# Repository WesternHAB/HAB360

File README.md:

# HAB360

This repository is for WesternU HAB team's VR balloon project. The goal is to fly 360° cameras on a balloon platform. The resulting video/images could then be viewed using VR cameras for outreach purposes.

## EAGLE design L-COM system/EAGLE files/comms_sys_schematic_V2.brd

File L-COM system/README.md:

# L-COM
This system is intended to serve as the communications system for high-altitude balloons and other devices in need of wireless communications.

The L-COM device may either be used as an attached radio by sending/receiving messages on the UART interface, or it may be programmed to be used as the sole onboard controller.

A python-based GUI is provided to allow full control over the L-COM device via a laptop, and may be adapted to be used as a groundstation.

## L-COM

 boards")

## Testing results
Initial testing involved the use of low-range, data-rate maximizing settings, while travelling throughout an urban environment. The L-COM modules behaved as expected, and the results produced were nominal for the environment. Communication was relatively unhindered by most residential buildings, and only encountered issues when blocked by large hills or certain non-residential buildings built with different materials.

Remaining testing involves long-range settings in a rural environment in order to provide a better estimate of how effective it will be for communicating with high-altitude balloons.

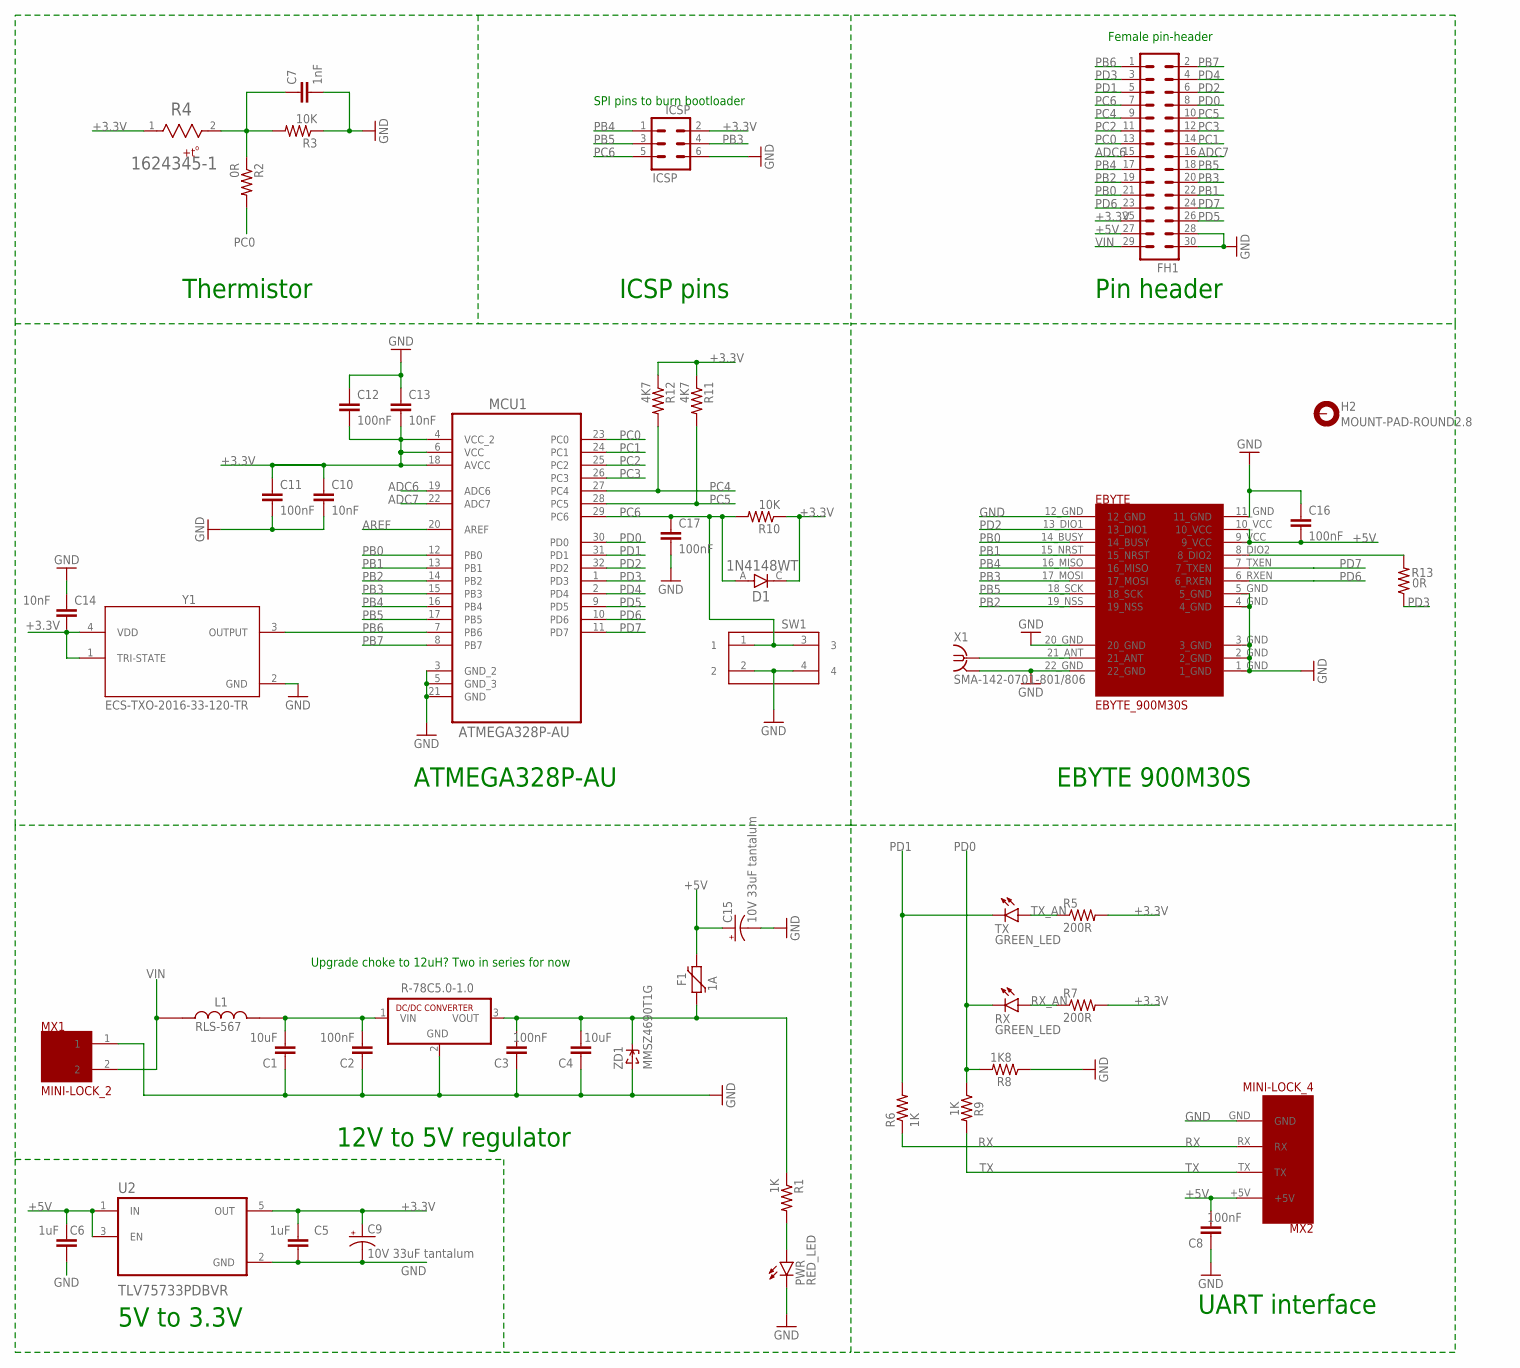
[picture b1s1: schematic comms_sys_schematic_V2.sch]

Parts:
C1, C4: 10uF; C0805
C2, C3, C8, C11, C12, C16, C17: 100nF; C0805
C5, C6: 1uF; C0805
C7: 1nF; C0805
C9, C15: 10V 33uF tantalum; CT3216
C10, C13, C14: 10nF; C0805
D1: 1N4148WT; SODFL1608X70N
EBYTE: EBYTE_900M30S; EBYTE_SX1262_900M30S_FOOTPRINT
F1: 1A; PTC0805
FH1: MA15-2
H2: MOUNT-PAD-ROUND2.8; 2,8-PAD
ICSP: ICSP; MA03-2
L1: RLS-567; IND_RLS-567
MCU1: ATMEGA328P-AU; QFP80P900X900X120-32N
MX1: MINI-LOCK_2
MX2: MINI-LOCK_4
PWR: RED_LED; CHIP-LED0805
R1, R6, R9: 1K; R0805
R2, R13: 0R; R0805
R3, R10: 10K; R0805
R4: 1624345-1; THRMC2012X50N
R5, R7: 200R; R0805
R8: 1K8; R0805
R11, R12: 4K7; R0805
RX: GREEN_LED; CHIP-LED0805
SW1: 430152043826
TX: GREEN_LED; CHIP-LED0805
U1: R-78C5.0-1.0; SIP3
U2: TLV75733PDBVR; SOT95P280X145-5N
X1: SMA-142-0701-801/806; J502-ND-142-0701-801/806
Y1: ECS-TXO-2016-33-120-TR; OSC_ECS-TXO-2016-33-120-TR
ZD1: MMSZ4690T1G; SOD-123

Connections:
$N77: C7.1, R2.1, R3.2, R4.2
+3.3V: C5.2, C9.+, C10.1, C11.1, C12.2, C13.2, C14.2, D1.C, FH1.25 (29), ICSP.2, MCU1.4 (VCC_2), MCU1.6 (VCC), MCU1.18 (AVCC), R4.1, R5.2, R7.2, R10.1, R11.1, R12.1, U2.5 (OUT), Y1.1 (TRI-STATE), Y1.4 (VDD)
+5V: C6.2, C8.2, C15.+, C16.2, EBYTE.9_VCC, EBYTE.10_VCC, F1.2, FH1.27 (31), MX2.+5V, U2.1 (IN), U2.3 (EN)
ADC6: FH1.15 (19), MCU1.19 (ADC6)
ADC7: FH1.16 (20), MCU1.22 (ADC7)
AREF: MCU1.20 (AREF)
GND: C1.1, C2.1, C3.1, C4.1, C5.1, C6.1, C7.2, C8.1, C9.-, C10.2, C11.2, C12.1, C13.1, C14.1, C15.-, C16.1, C17.2, EBYTE.1_GND, EBYTE.2_GND, EBYTE.3_GND, EBYTE.4_GND, EBYTE.5_GND, EBYTE.11_GND, EBYTE.12_GND, EBYTE.20_GND, EBYTE.22_GND, FH1.28 (32), FH1.30 (34), ICSP.6, MCU1.3 (GND_2), MCU1.5 (GND_3), MCU1.21 (GND), MX1.1, MX2.GND, PWR.C, R3.1, R8.1, SW1.2, SW1.4, U1.2 (GND), U2.2 (GND), X1.G@1 (2), X1.G@2 (2), X1.G@3 (2), X1.G@4 (2), Y1.2 (GND), ZD1.A
unnamed: C3.2, C4.2, F1.1, R1.1, U1.3 (VOUT), ZD1.C
unnamed: EBYTE.8_DIO2, R13.2
unnamed: PWR.A, R1.2
unnamed: EBYTE.21_ANT, X1.1
unnamed: C1.2, C2.2, L1.2, U1.1 (VIN)
PB0: EBYTE.14_BUSY, FH1.21 (25), MCU1.12 (PB0)
PB1: EBYTE.15_NRST, FH1.22 (26), MCU1.13 (PB1)
PB2: EBYTE.19_NSS, FH1.19 (23), MCU1.14 (PB2)
PB3: EBYTE.17_MOSI, FH1.20 (24), ICSP.4, MCU1.15 (PB3)
PB4: EBYTE.16_MISO, FH1.17 (21), ICSP.1, MCU1.16 (PB4)
PB5: EBYTE.18_SCK, FH1.18 (22), ICSP.3, MCU1.17 (PB5)
PB6: FH1.1 (5), MCU1.7 (PB6), Y1.3 (OUTPUT)
PB7: FH1.2 (6), MCU1.8 (PB7)
PC0: FH1.13 (17), MCU1.23 (PC0), R2.2
PC1: FH1.14 (18), MCU1.24 (PC1)
PC2: FH1.11 (15), MCU1.25 (PC2)
PC3: FH1.12 (16), MCU1.26 (PC3)
PC4: FH1.9 (13), MCU1.27 (PC4), R12.2
PC5: FH1.10 (14), MCU1.28 (PC5), R11.2
PC6: C17.1, D1.A, FH1.7 (11), ICSP.5, MCU1.29 (PC6), R10.2, SW1.1, SW1.3
PD0: FH1.8 (12), MCU1.30 (PD0), R8.2, R9.1, RX.C
PD1: FH1.5 (9), MCU1.31 (PD1), R6.2, TX.C
PD2: EBYTE.13_DIO1, FH1.6 (10), MCU1.32 (PD2)
PD3: FH1.3 (7), MCU1.1 (PD3), R13.1
PD4: FH1.4 (8), MCU1.2 (PD4)
PD5: FH1.26 (30), MCU1.9 (PD5)
PD6: EBYTE.6_RXEN, FH1.23 (27), MCU1.10 (PD6)
PD7: EBYTE.7_TXEN, FH1.24 (28), MCU1.11 (PD7)
RX: MX2.RX, R6.1
RX_AN: R7.1, RX.A
TX: MX2.TX, R9.2
TX_AN: R5.1, TX.A
VIN: FH1.29 (33), L1.1, MX1.2

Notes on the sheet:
SPI pins to burn bootloader
12V to 5V regulator
Upgrade choke to 12uH? Two in series for now
UART interface
5V to 3.3V
ATMEGA328P-AU
EBYTE 900M30S
Pin header
ICSP pins
Thermistor
Female pin-header

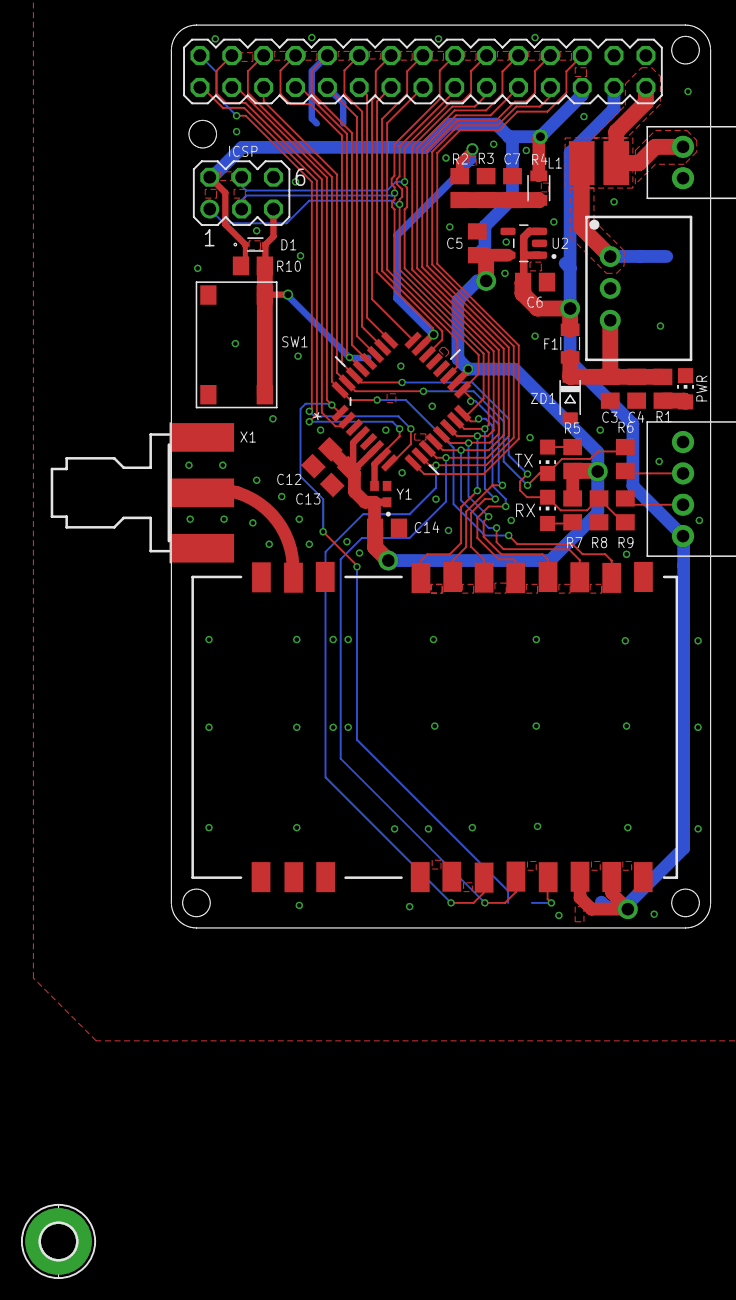
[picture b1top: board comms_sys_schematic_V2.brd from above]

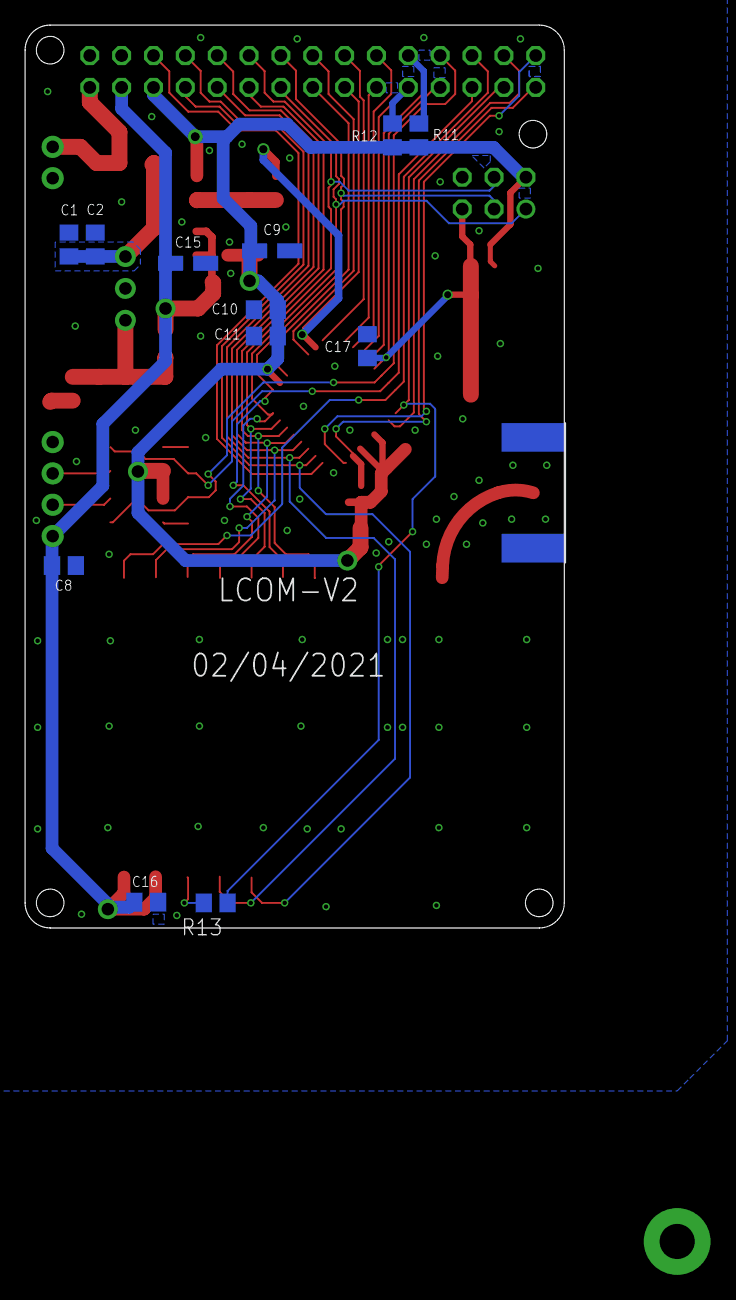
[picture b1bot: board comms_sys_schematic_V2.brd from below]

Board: 2 copper layers, 43.0 x 72.0 mm, 49 parts (12 on the bottom side), 39 nets.

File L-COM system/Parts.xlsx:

Part type: | Capacitors |  |  |  | Part type: | Resistors |  |  |  | Part type: | Inductors
Name | Footprint | Value | Notes |  | Name | Footprint | Value | Notes |  | Name | Footprint | Value | Notes
C1 | 0805 | 10uF | 50V min |  | R1 | 0805 | 1K |  |  | L1 | CD43 | 5.6uH | RLS-567, 12-48V?
C2 | 0805 | 100nF | 50V min |  | R2 | 0805 | 0R
C3 | 0805 | 100nF |  |  | R3 | 0805 | 10K
C4 | 0805 | 10uF |  |  | R4 | 0805 | 10K-Therm | Thermistor |  | Part type: | Diodes
C5 | 0805 | 1uF |  |  | R5 | 0805 | 200R |  |  | Name | Footprint | Model | Notes
C6 | 0805 | 1uF |  |  | R6 | 0805 | 1K |  |  | D1 | 0603 | 1N4148WT
C7 | 0805 | 1nF |  |  | R7 | 0805 | 200R |  |  | ZD1 | 1206 | MMSZ4690T1G
C8 | 0805 | 100nF |  |  | R8 | 0805 | 1K8
C9 | 1206 (3216) | 33uF | 10V tantalum |  | R9 | 0805 | 1K
C10 | 0805 | 10nF |  |  | R10 | 0805 | 10K |  |  | Part type: | LEDs
C11 | 0805 | 100nF |  |  | R11 | 0805 | 4K7 |  |  | Name | Footprint | Colour | Notes
C12 | 0805 | 100nF |  |  | R12 | 0805 | 4K7 |  |  | LED_TX | 0805 | Green
C13 | 0805 | 10nF |  |  | R13 | 0805 | 0R |  |  | LED_RX | 0805 | Green
C14 | 0805 | 10nF |  |  | R13 | 0805 | 0R |  |  | LED_PWR | 0805 | Red
C15 | 1206 (3216) | 33uF | 10V tantalum
C16 | 0805 | 100nF
C17 | 1206 | 100nF
Part type: | Connectors |  |  |  | Part type: | Voltage regulators |  |  |  | Part type: | Microcontroller
Name | Type |  | Notes |  | Name | Type |  | Notes |  | Name | Part |  | Notes
ICSP | 6-pin ICSP |  |  |  | U1 | R-78C5.0-1.0 |  |  |  | MCU1 | ATMEGA328P-AU |  |  | Need a 328 for program memory and SRAM requirements.
MX1 | 2-pin Molex Mini-Lock |  |  |  | U2 | TLV75733PDBVR |  |  |  | Y1 | ECS-TXO-2016-33-120-TR |  | Clock source
MX2 | 4-pin Molex Mini-Lock
FH1 | 2x15 2.54mm pitch female header
X1 | SMA edge-connector (plug, male pin) |  |  |  |  |  |  |  |  | Part type: | Fuses
 |  |  |  |  |  |  |  |  |  | Name | Footprint | Value | Model | Notes
 |  |  |  |  |  |  |  |  |  | F1 | 0805 | 1A
Part type: | Miscellaneous
Name | Type |  | Notes
SW1 | Tactile switch
EBYTE | EBYTE_900M_30S
4x M2 screws

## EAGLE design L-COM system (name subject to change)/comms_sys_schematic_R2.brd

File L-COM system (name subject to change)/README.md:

# LCOM

Image gallery of board (slightly outdated):
https://imgur.com/a/dvTlvwL

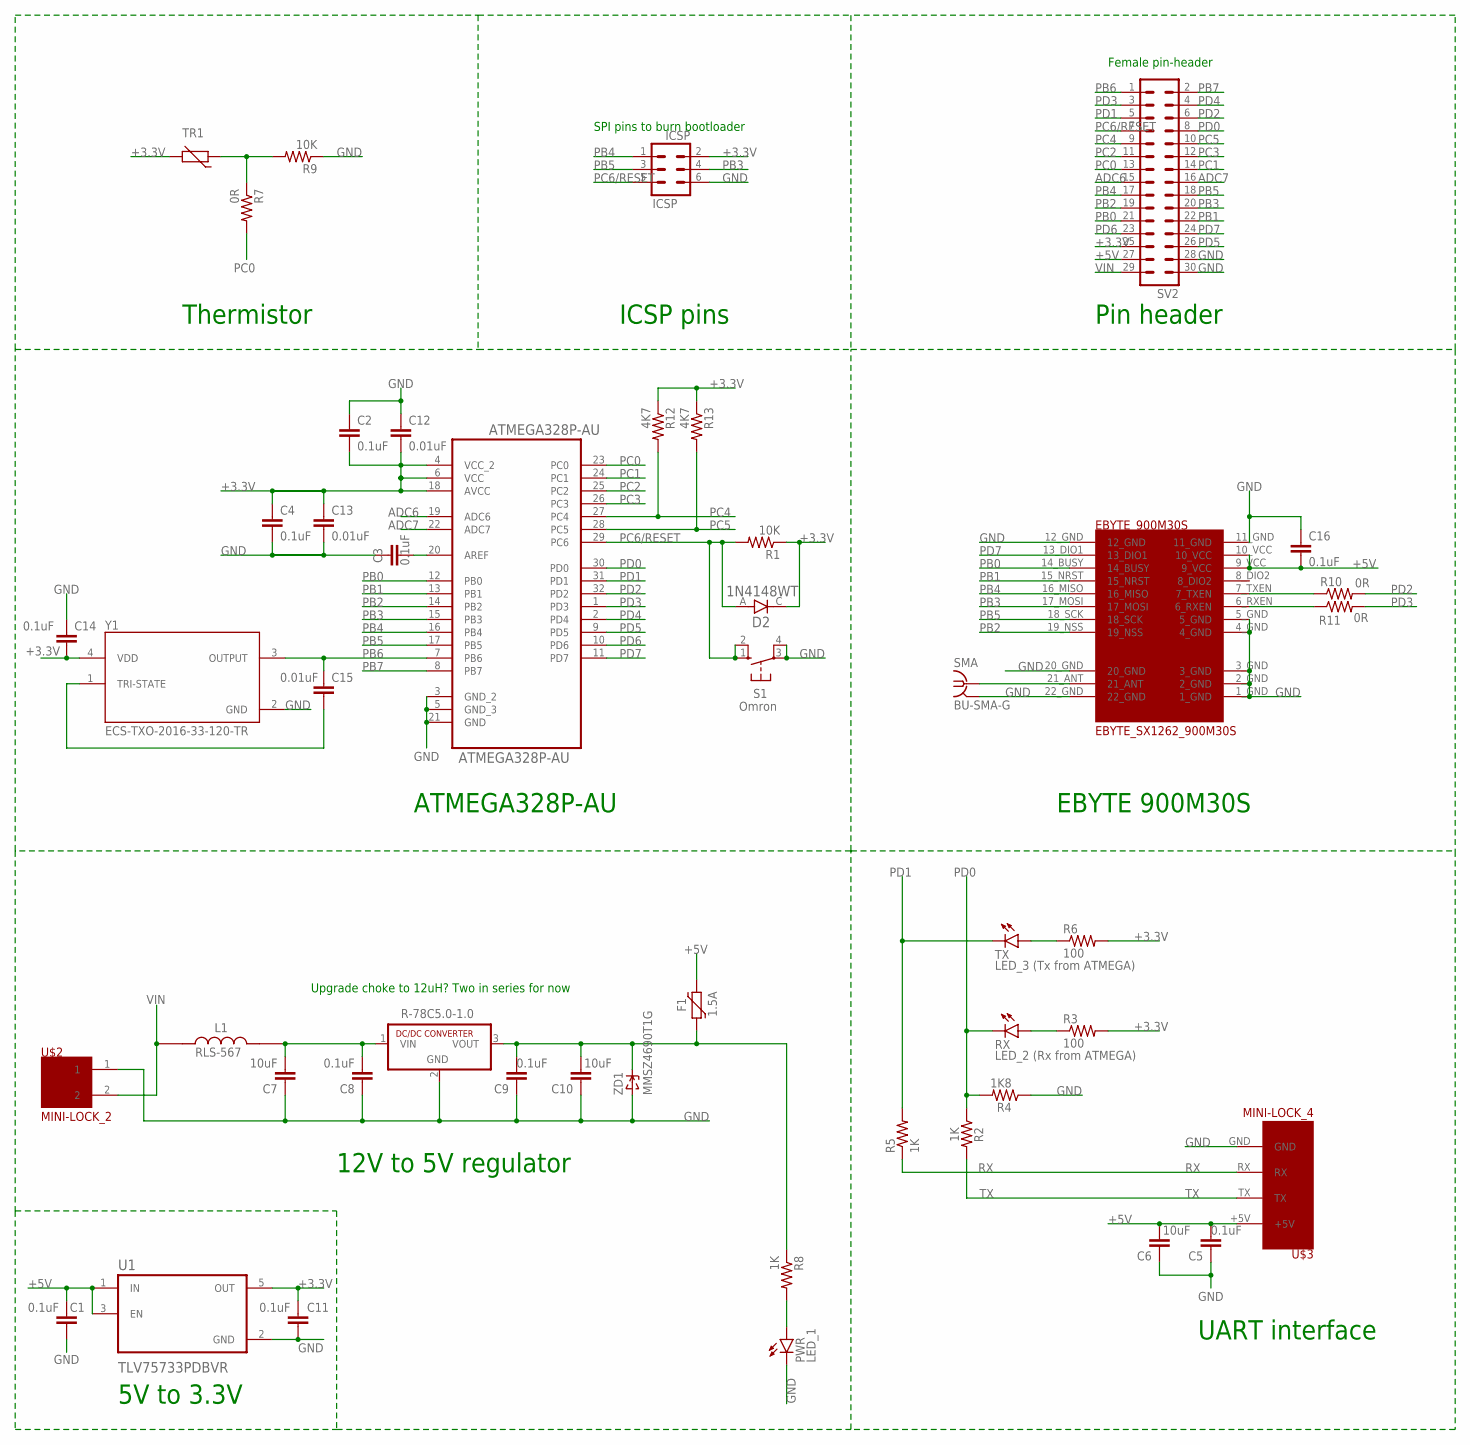
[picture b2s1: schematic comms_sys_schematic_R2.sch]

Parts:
ATMEGA328P-AU: ATMEGA328P-AU; QFP80P900X900X120-32N
C1, C2, C3, C4, C5, C8, C9, C11, C14, C16: 0.1uF; C0805
C6, C7, C10: 10uF; C0805
C12, C13, C15: 0.01uF; C0805
D2: 1N4148WT; SODFL1608X70N
EBYTE_900M30S: EBYTE_SX1262_900M30S; EBYTE_SX1262_900M30S_FOOTPRINT
F1: 1.5A; PTC0805
ICSP: ICSP; MA03-2
L1: RLS-567; IND_RLS-567
PWR: LED_1; CHIP-LED0805
R1, R9: 10K; R0805
R2, R5, R8: 1K; R0805
R3, R6: 100; R0805
R4: 1K8; R0805
R7, R10, R11: 0R; R0805
R12, R13: 4K7; R0805
R-78C5.0-1.0: R-78C5.0-1.0; SIP3
RX: LED_2 (Rx from ATMEGA); CHIP-LED0805
S1: Omron; B3F-10XX
SMA: BU-SMA-G
SV2: MA15-2
TR1: THERMISTOR_R-2,5; RS-2,5
TX: LED_3 (Tx from ATMEGA); CHIP-LED0805
U1: TLV75733PDBVR; SOT95P280X145-5N
U$2: MINI-LOCK_2
U$3: MINI-LOCK_4
Y1: ECS-TXO-2016-33-120-TR; OSC_ECS-TXO-2016-33-120-TR
ZD1: MMSZ4690T1G; SOD-123

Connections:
$N77: R7.1, R9.2, TR1.1
+3.3V: ATMEGA328P-AU.4 (VCC_2), ATMEGA328P-AU.6 (VCC), ATMEGA328P-AU.18 (AVCC), C2.2, C4.1, C11.2, C12.2, C13.1, C14.2, D2.C, ICSP.2, R1.1, R3.2, R6.2, R12.1, R13.1, SV2.25 (29), TR1.2, U1.5 (OUT), Y1.4 (VDD)
+5V: C1.2, C5.2, C6.2, C16.2, EBYTE_900M30S.9_VCC, EBYTE_900M30S.10_VCC, F1.2, SV2.27 (31), U1.1 (IN), U1.3 (EN), U$3.+5V
ADC6: ATMEGA328P-AU.19 (ADC6), SV2.15 (19)
ADC7: ATMEGA328P-AU.22 (ADC7), SV2.16 (20)
GND: ATMEGA328P-AU.3 (GND_2), ATMEGA328P-AU.5 (GND_3), ATMEGA328P-AU.21 (GND), C1.1, C2.1, C3.1, C4.2, C5.1, C6.1, C7.1, C8.1, C9.1, C10.1, C11.1, C12.1, C13.2, C14.1, C16.1, EBYTE_900M30S.1_GND, EBYTE_900M30S.2_GND, EBYTE_900M30S.3_GND, EBYTE_900M30S.4_GND, EBYTE_900M30S.5_GND, EBYTE_900M30S.11_GND, EBYTE_900M30S.12_GND, EBYTE_900M30S.20_GND, EBYTE_900M30S.22_GND, ICSP.6, PWR.C, R4.1, R9.1, R-78C5.0-1.0.2 (GND), S1.3, S1.4 (P1), SMA.2, SMA.3 (2), SMA.4 (2), SMA.5 (2), SV2.28 (32), SV2.30 (34), U1.2 (GND), U$2.1, U$3.GND, Y1.2 (GND), ZD1.A
unnamed: C9.2, C10.2, F1.1, R8.1, R-78C5.0-1.0.3 (VOUT), ZD1.C
unnamed: PWR.A, R8.2
unnamed: C15.2, Y1.1 (TRI-STATE)
unnamed: EBYTE_900M30S.7_TXEN, R10.1
unnamed: EBYTE_900M30S.6_RXEN, R11.1
unnamed: EBYTE_900M30S.21_ANT, SMA.1
unnamed: R3.1, RX.A
unnamed: ATMEGA328P-AU.20 (AREF), C3.2
unnamed: R6.1, TX.A
unnamed: C7.2, C8.2, L1.2, R-78C5.0-1.0.1 (VIN)
PB0: ATMEGA328P-AU.12 (PB0), EBYTE_900M30S.14_BUSY, SV2.21 (25)
PB1: ATMEGA328P-AU.13 (PB1), EBYTE_900M30S.15_NRST, SV2.22 (26)
PB2: ATMEGA328P-AU.14 (PB2), EBYTE_900M30S.19_NSS, SV2.19 (23)
PB3: ATMEGA328P-AU.15 (PB3), EBYTE_900M30S.17_MOSI, ICSP.4, SV2.20 (24)
PB4: ATMEGA328P-AU.16 (PB4), EBYTE_900M30S.16_MISO, ICSP.1, SV2.17 (21)
PB5: ATMEGA328P-AU.17 (PB5), EBYTE_900M30S.18_SCK, ICSP.3, SV2.18 (22)
PB6: ATMEGA328P-AU.7 (PB6), C15.1, SV2.1 (5), Y1.3 (OUTPUT)
PB7: ATMEGA328P-AU.8 (PB7), SV2.2 (6)
PC0: ATMEGA328P-AU.23 (PC0), R7.2, SV2.13 (17)
PC1: ATMEGA328P-AU.24 (PC1), SV2.14 (18)
PC2: ATMEGA328P-AU.25 (PC2), SV2.11 (15)
PC3: ATMEGA328P-AU.26 (PC3), SV2.12 (16)
PC4: ATMEGA328P-AU.27 (PC4), R12.2, SV2.9 (13)
PC5: ATMEGA328P-AU.28 (PC5), R13.2, SV2.10 (14)
PC6/RESET: ATMEGA328P-AU.29 (PC6), D2.A, ICSP.5, R1.2, S1.1 (S), S1.2 (S1), SV2.7 (11)
PD0: ATMEGA328P-AU.30 (PD0), R2.1, R4.2, RX.C, SV2.8 (12)
PD1: ATMEGA328P-AU.31 (PD1), R5.2, SV2.5 (9), TX.C
PD2: ATMEGA328P-AU.32 (PD2), R10.2, SV2.6 (10)
PD3: ATMEGA328P-AU.1 (PD3), R11.2, SV2.3 (7)
PD4: ATMEGA328P-AU.2 (PD4), SV2.4 (8)
PD5: ATMEGA328P-AU.9 (PD5), SV2.26 (30)
PD6: ATMEGA328P-AU.10 (PD6), SV2.23 (27)
PD7: ATMEGA328P-AU.11 (PD7), EBYTE_900M30S.13_DIO1, SV2.24 (28)
RX: R5.1, U$3.RX
TX: R2.2, U$3.TX
VIN: L1.1, SV2.29 (33), U$2.2

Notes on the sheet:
SPI pins to burn bootloader
12V to 5V regulator
Upgrade choke to 12uH? Two in series for now
UART interface
5V to 3.3V
ATMEGA328P-AU
EBYTE 900M30S
Pin header
ICSP pins
Thermistor
Female pin-header

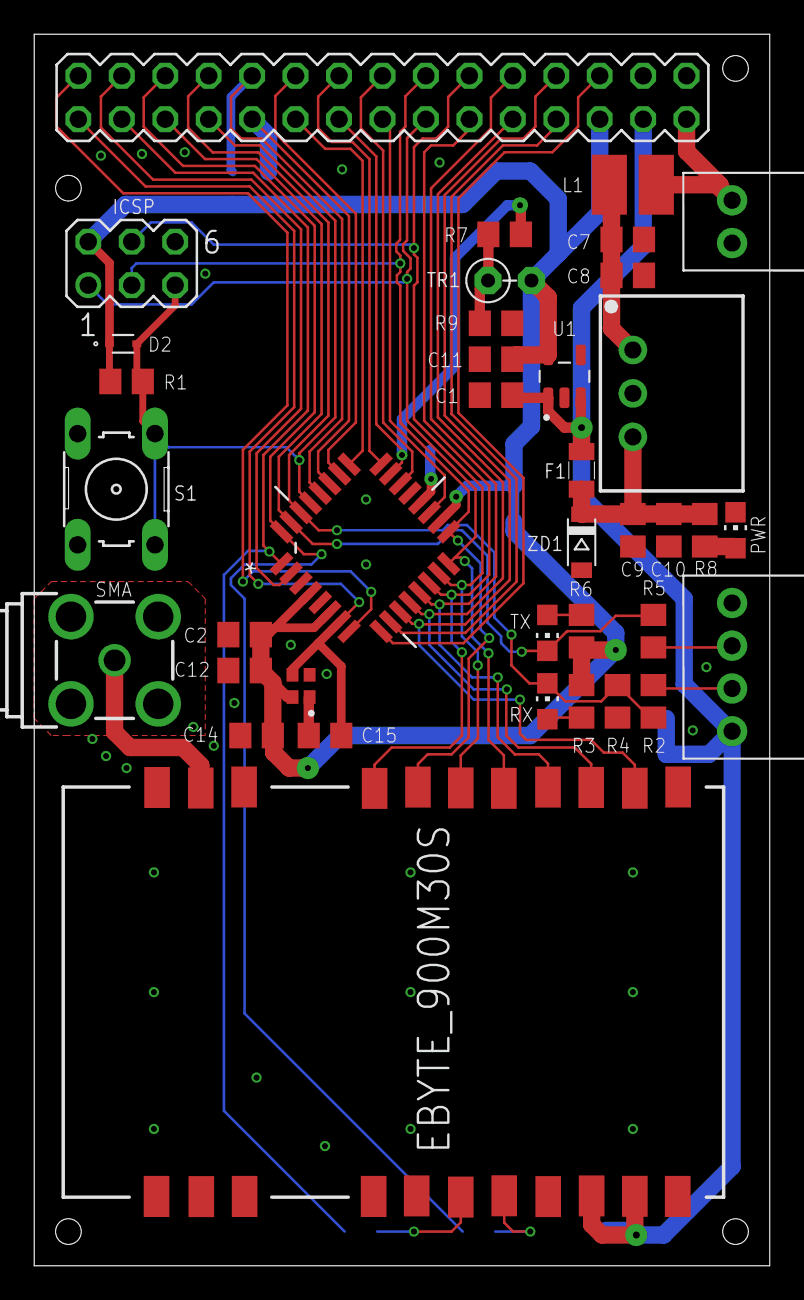
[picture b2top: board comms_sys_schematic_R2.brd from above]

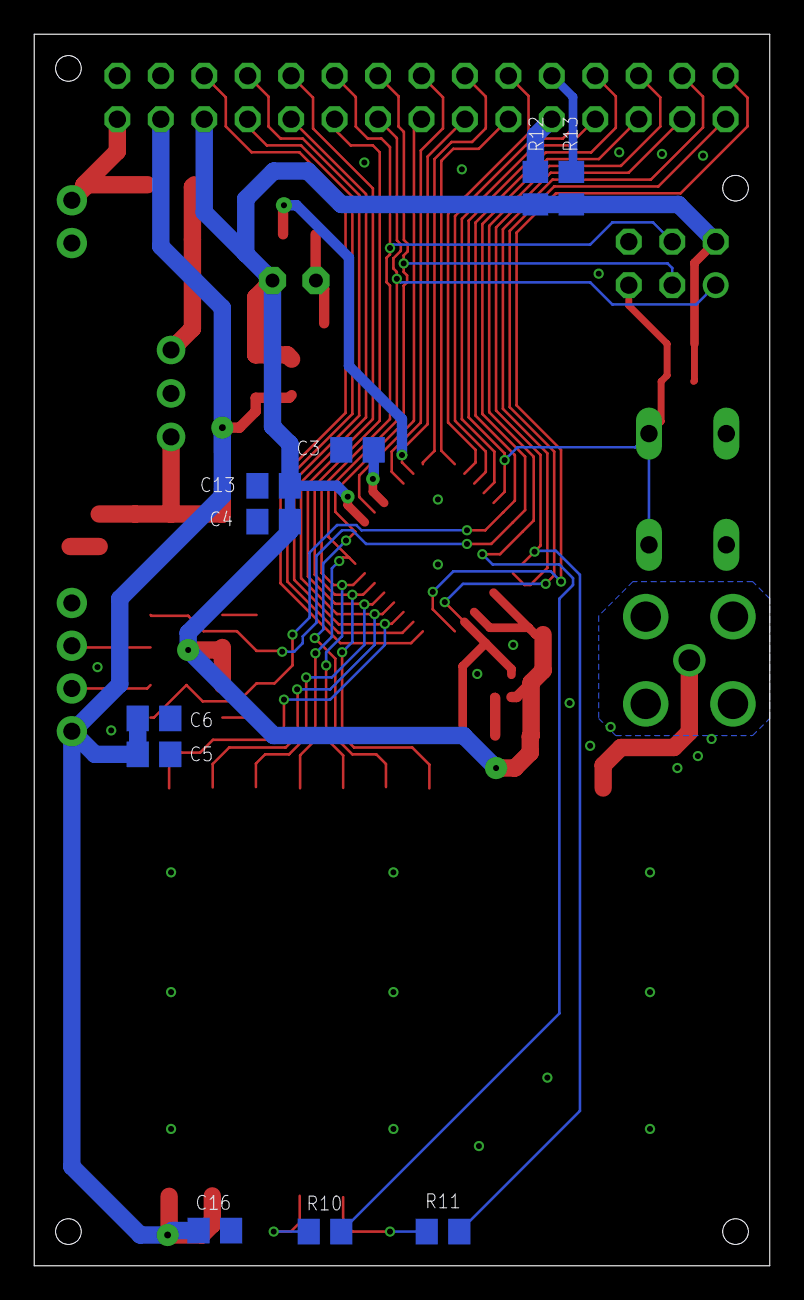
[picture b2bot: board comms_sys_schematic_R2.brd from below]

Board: 2 copper layers, 43.0 x 72.0 mm, 48 parts (10 on the bottom side), 42 nets.

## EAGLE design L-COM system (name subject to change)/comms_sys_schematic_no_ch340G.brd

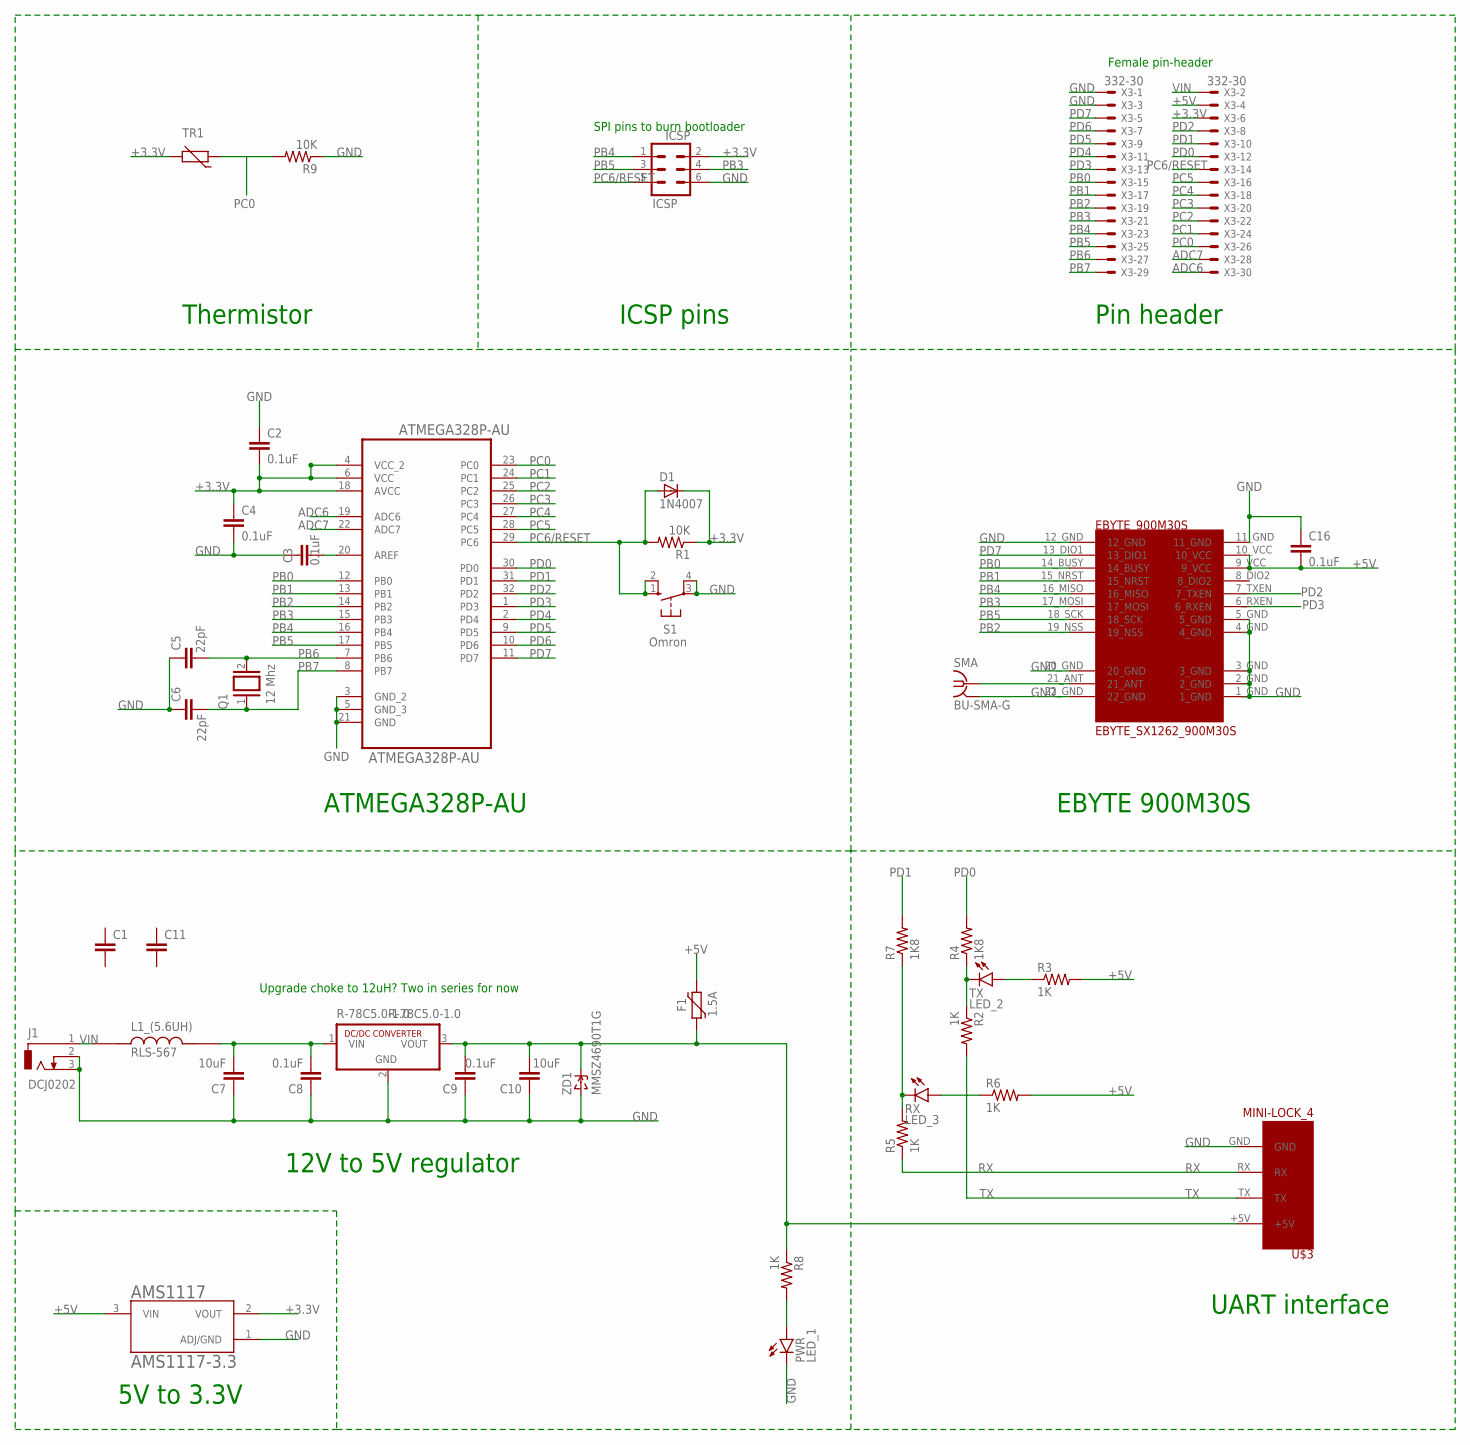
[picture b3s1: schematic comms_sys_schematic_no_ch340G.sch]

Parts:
AMS1117: AMS1117-3.3; SOT229P700X180-4N
ATMEGA328P-AU: ATMEGA328P-AU; QFP80P900X900X120-32N
C1, C11: C-EUC1206; C1206
C2, C3, C4, C8, C9, C16: 0.1uF; C0805
C5, C6: 22pF; C0805
C7, C10: 10uF; C0805
D1: 1N4007; SMA
EBYTE_900M30S: EBYTE_SX1262_900M30S; EBYTE_SX1262_900M30S_FOOTPRINT
F1: 1.5A; PTC0805
ICSP: ICSP; MA03-2
J1: DCJ0202
L1_(5.6UH): RLS-567; IND_RLS-567
PWR: LED_1; CHIP-LED0805
Q1: 12 Mhz; QS
R1, R9: 10K; R0805
R2, R3, R5, R6, R8: 1K; R0805
R4, R7: 1K8; R0805
R-78C5.0-1.0: R-78C5.0-1.0; SIP3
RX: LED_3; CHIP-LED0805
S1: Omron; B3F-10XX
SMA: BU-SMA-G
TR1: THERMISTOR_R-2,5; RS-2,5
TX: LED_2; CHIP-LED0805
U$3: MINI-LOCK_4
X3: 332-30
ZD1: MMSZ4690T1G; SOD-123

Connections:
+3.3V: AMS1117.2 (VOUT), ATMEGA328P-AU.4 (VCC_2), ATMEGA328P-AU.6 (VCC), ATMEGA328P-AU.18 (AVCC), C2.2, C4.1, D1.K (C), ICSP.2, R1.1, TR1.2, X3.6
+5V: AMS1117.3 (VIN), C16.2, EBYTE_900M30S.9_VCC, EBYTE_900M30S.10_VCC, F1.2, R3.2, R6.2, X3.4
ADC6: ATMEGA328P-AU.19 (ADC6), X3.30
ADC7: ATMEGA328P-AU.22 (ADC7), X3.28
GND: AMS1117.1 (ADJ/GND), ATMEGA328P-AU.3 (GND_2), ATMEGA328P-AU.5 (GND_3), ATMEGA328P-AU.21 (GND), C2.1, C3.1, C4.2, C5.1, C6.1, C7.1, C8.1, C9.1, C10.1, C16.1, EBYTE_900M30S.1_GND, EBYTE_900M30S.2_GND, EBYTE_900M30S.3_GND, EBYTE_900M30S.4_GND, EBYTE_900M30S.5_GND, EBYTE_900M30S.11_GND, EBYTE_900M30S.12_GND, EBYTE_900M30S.20_GND, EBYTE_900M30S.22_GND, ICSP.6, J1.2, J1.3, PWR.C, R9.1, R-78C5.0-1.0.2 (GND), S1.3, S1.4 (P1), SMA.2, SMA.3 (2), SMA.4 (2), SMA.5 (2), U$3.GND, X3.1, X3.3, ZD1.A
unnamed: C9.2, C10.2, F1.1, R8.1, R-78C5.0-1.0.3 (VOUT), U$3.+5V, ZD1.C
unnamed: PWR.A, R8.2
unnamed: EBYTE_900M30S.21_ANT, SMA.1
unnamed: R3.1, TX.A
unnamed: ATMEGA328P-AU.20 (AREF), C3.2
unnamed: R6.1, RX.A
unnamed: R2.1, R4.1, TX.C
unnamed: R5.2, R7.1, RX.C
unnamed: C7.2, C8.2, L1_(5.6UH).2, R-78C5.0-1.0.1 (VIN)
PB0: ATMEGA328P-AU.12 (PB0), EBYTE_900M30S.14_BUSY, X3.15
PB1: ATMEGA328P-AU.13 (PB1), EBYTE_900M30S.15_NRST, X3.17
PB2: ATMEGA328P-AU.14 (PB2), EBYTE_900M30S.19_NSS, X3.19
PB3: ATMEGA328P-AU.15 (PB3), EBYTE_900M30S.17_MOSI, ICSP.4, X3.21
PB4: ATMEGA328P-AU.16 (PB4), EBYTE_900M30S.16_MISO, ICSP.1, X3.23
PB5: ATMEGA328P-AU.17 (PB5), EBYTE_900M30S.18_SCK, ICSP.3, X3.25
PB6: ATMEGA328P-AU.7 (PB6), C5.2, Q1.2, X3.27
PB7: ATMEGA328P-AU.8 (PB7), C6.2, Q1.1, X3.29
PC0: ATMEGA328P-AU.23 (PC0), R9.2, TR1.1, X3.26
PC1: ATMEGA328P-AU.24 (PC1), X3.24
PC2: ATMEGA328P-AU.25 (PC2), X3.22
PC3: ATMEGA328P-AU.26 (PC3), X3.20
PC4: ATMEGA328P-AU.27 (PC4), X3.18
PC5: ATMEGA328P-AU.28 (PC5), X3.16
PC6/RESET: ATMEGA328P-AU.29 (PC6), D1.A, ICSP.5, R1.2, S1.1 (S), S1.2 (S1), X3.14
PD0: ATMEGA328P-AU.30 (PD0), R4.2, X3.12
PD1: ATMEGA328P-AU.31 (PD1), R7.2, X3.10
PD2: ATMEGA328P-AU.32 (PD2), EBYTE_900M30S.7_TXEN, X3.8
PD3: ATMEGA328P-AU.1 (PD3), EBYTE_900M30S.6_RXEN, X3.13
PD4: ATMEGA328P-AU.2 (PD4), X3.11
PD5: ATMEGA328P-AU.9 (PD5), X3.9
PD6: ATMEGA328P-AU.10 (PD6), X3.7
PD7: ATMEGA328P-AU.11 (PD7), EBYTE_900M30S.13_DIO1, X3.5
RX: R5.1, U$3.RX
TX: R2.2, U$3.TX
VIN: J1.1, L1_(5.6UH).1, X3.2

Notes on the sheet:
SPI pins to burn bootloader
12V to 5V regulator
Upgrade choke to 12uH? Two in series for now
Female pin-header
UART interface
5V to 3.3V
ATMEGA328P-AU
EBYTE 900M30S
Pin header
ICSP pins
Thermistor

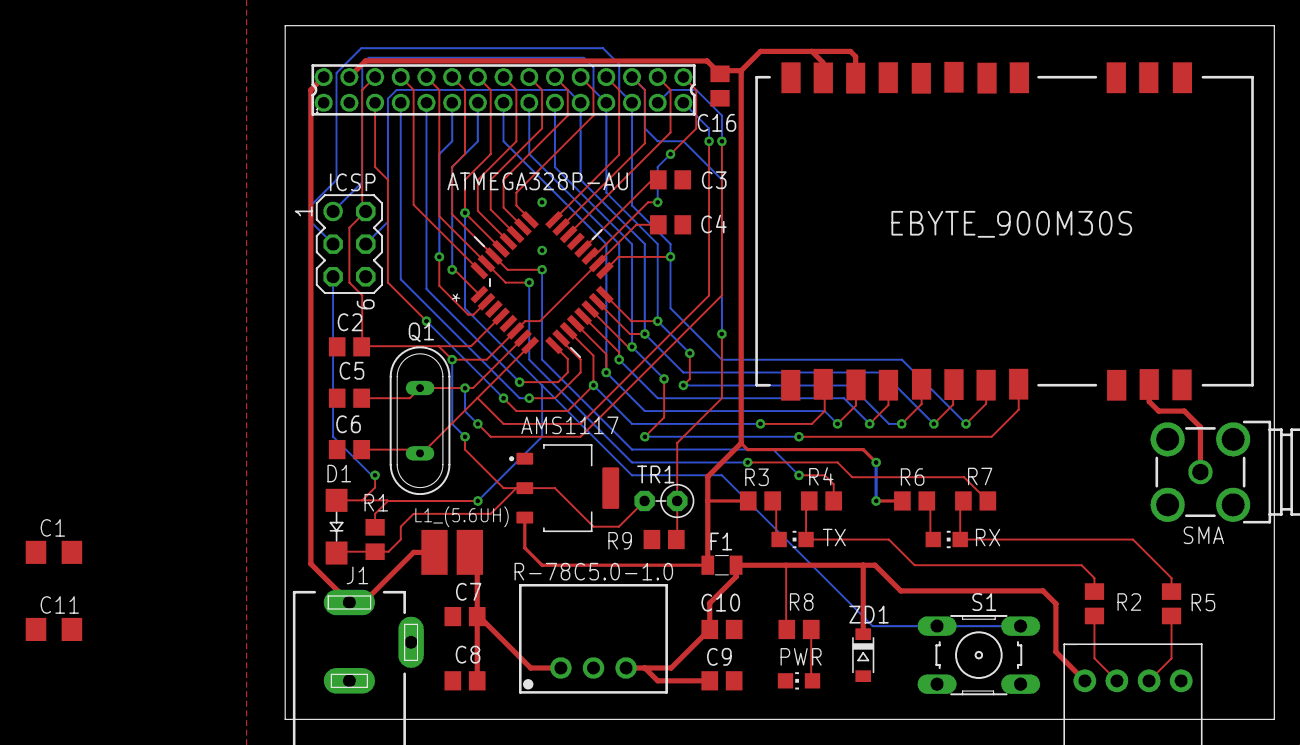
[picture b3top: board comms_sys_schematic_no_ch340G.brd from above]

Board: 2 copper layers, 77.0 x 54.0 mm, 40 parts (0 on the bottom side), 40 nets.

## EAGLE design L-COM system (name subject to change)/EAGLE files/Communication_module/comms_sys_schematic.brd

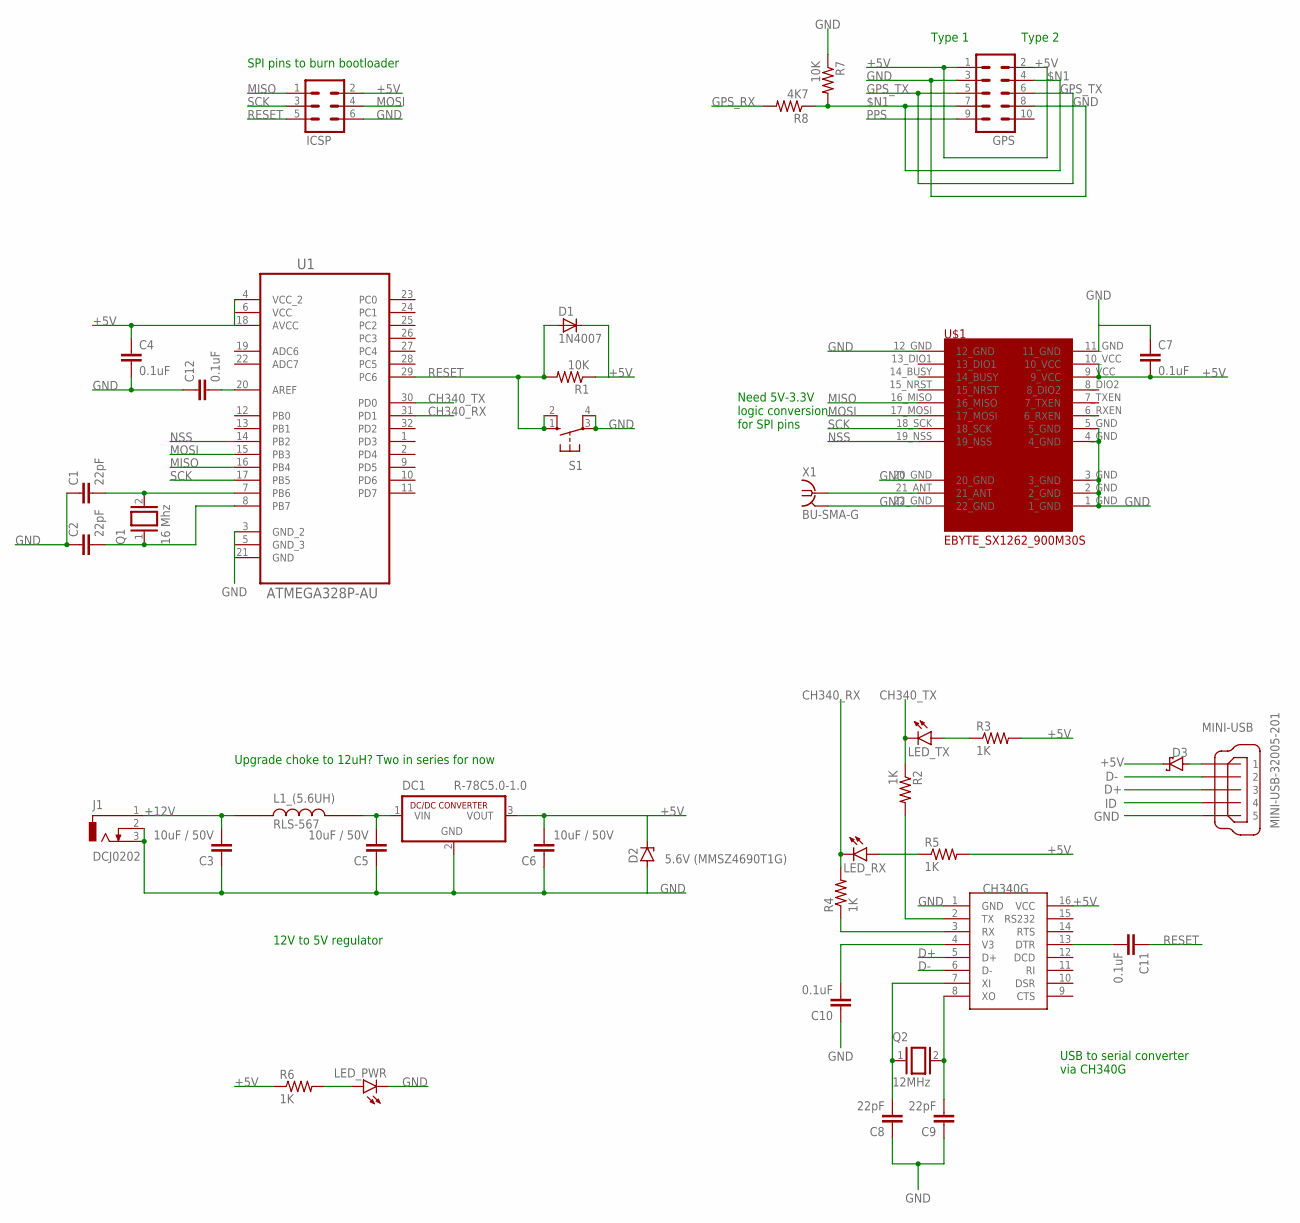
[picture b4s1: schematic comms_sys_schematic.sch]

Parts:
C1, C2, C8, C9: 22pF; C2.5-3
C3, C5, C6: 10uF / 50V; C2.5-3
C4, C7, C10, C11, C12: 0.1uF; C2.5-3
D1: 1N4007; SMA
D2: 5.6V (MMSZ4690T1G); DO41Z10
D3: SCHOTTKY-DIODESMD; SMB
DC1: R-78C5.0-1.0; SIP3
GPS: MA05-2
ICSP: MA03-2
J1: DCJ0202
L1_(5.6UH): RLS-567; IND_RLS-567
LED_PWR: LEDCHIP-LED0805; CHIP-LED0805
LED_RX: LEDCHIP-LED0805; CHIP-LED0805
LED_TX: LEDCHIP-LED0805; CHIP-LED0805
MINI-USB: MINI-USB-32005-201; 32005-201
Q1: 16 Mhz; QS
Q2: 12MHz; QS
R1, R7: 10K; R0805
R2, R3, R4, R5, R6: 1K; R0805
R8: 4K7; R0805
S1: 10-XX; B3F-10XX
U1: ATMEGA328P-AU; QFP80P900X900X120-32N
U$1: EBYTE_SX1262_900M30S; EBYTE_SX1262_900M30S_FOOTPRINT
U$2: CH340G; SOIC16
X1: BU-SMA-G

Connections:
$N1: GPS.4, GPS.7, R7.2, R8.1
+5V: C4.1, C6.2, C7.2, D1.K (C), D2.C, D3.C, DC1.3 (VOUT), GPS.1, GPS.2, ICSP.2, R1.1, R3.2, R5.2, R6.1, U1.4 (VCC_2), U1.6 (VCC), U1.18 (AVCC), U$1.9_VCC, U$1.10_VCC, U$2.16 (VCC)
+12V: C3.2, J1.1, L1_(5.6UH).1
CH340_RX: LED_RX.C, R4.2, U1.31 (PD1)
CH340_TX: LED_TX.C, R2.1, U1.30 (PD0)
D+: MINI-USB.3, U$2.5 (D+)
D-: MINI-USB.2, U$2.6 (D-)
GND: C1.1, C2.1, C3.1, C4.2, C5.1, C6.1, C7.1, C8.1, C9.1, C10.1, C12.1, D2.A, DC1.2 (GND), GPS.3, GPS.8, ICSP.6, J1.2, J1.3, LED_PWR.C, MINI-USB.5, R7.1, S1.3, S1.4 (P1), U1.3 (GND_2), U1.5 (GND_3), U1.21 (GND), U$1.1_GND, U$1.2_GND, U$1.3_GND, U$1.4_GND, U$1.5_GND, U$1.11_GND, U$1.12_GND, U$1.20_GND, U$1.22_GND, U$2.1 (GND), X1.2, X1.3 (2), X1.4 (2), X1.5 (2)
GPS_RX: R8.2
GPS_TX: GPS.5, GPS.6
ID: MINI-USB.4
MISO: ICSP.1, U1.16 (PB4), U$1.16_MISO
MOSI: ICSP.4, U1.15 (PB3), U$1.17_MOSI
unnamed: C1.2, Q1.2, U1.7 (PB6)
unnamed: C2.2, Q1.1, U1.8 (PB7)
unnamed: C8.2, Q2.1, U$2.7 (XI)
unnamed: LED_PWR.A, R6.2
unnamed: C9.2, Q2.2, U$2.8 (XO)
unnamed: C5.2, DC1.1 (VIN), L1_(5.6UH).2
unnamed: D3.A, MINI-USB.1
unnamed: U$1.21_ANT, X1.1
unnamed: C10.2, U$2.4 (V3)
unnamed: C11.2, U$2.13 (DTR)
unnamed: R2.2, U$2.2 (TX)
unnamed: LED_TX.A, R3.1
unnamed: R4.1, U$2.3 (RX)
unnamed: C12.2, U1.20 (AREF)
unnamed: LED_RX.A, R5.1
NSS: U1.14 (PB2), U$1.19_NSS
PPS: GPS.9
RESET: C11.1, D1.A, ICSP.5, R1.2, S1.1 (S), S1.2 (S1), U1.29 (PC6)
SCK: ICSP.3, U1.17 (PB5), U$1.18_SCK

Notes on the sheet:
SPI pins to burn bootloader
USB to serial converter via CH340G
12V to 5V regulator
Type 1
Type 2
Upgrade choke to 12uH? Two in series for now
Need 5V-3.3V logic conversion for SPI pins

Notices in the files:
parts and their libraries:
Wurth_Elektronik_Electromechanic_Switch_: Copyright: Würth Elektronik
